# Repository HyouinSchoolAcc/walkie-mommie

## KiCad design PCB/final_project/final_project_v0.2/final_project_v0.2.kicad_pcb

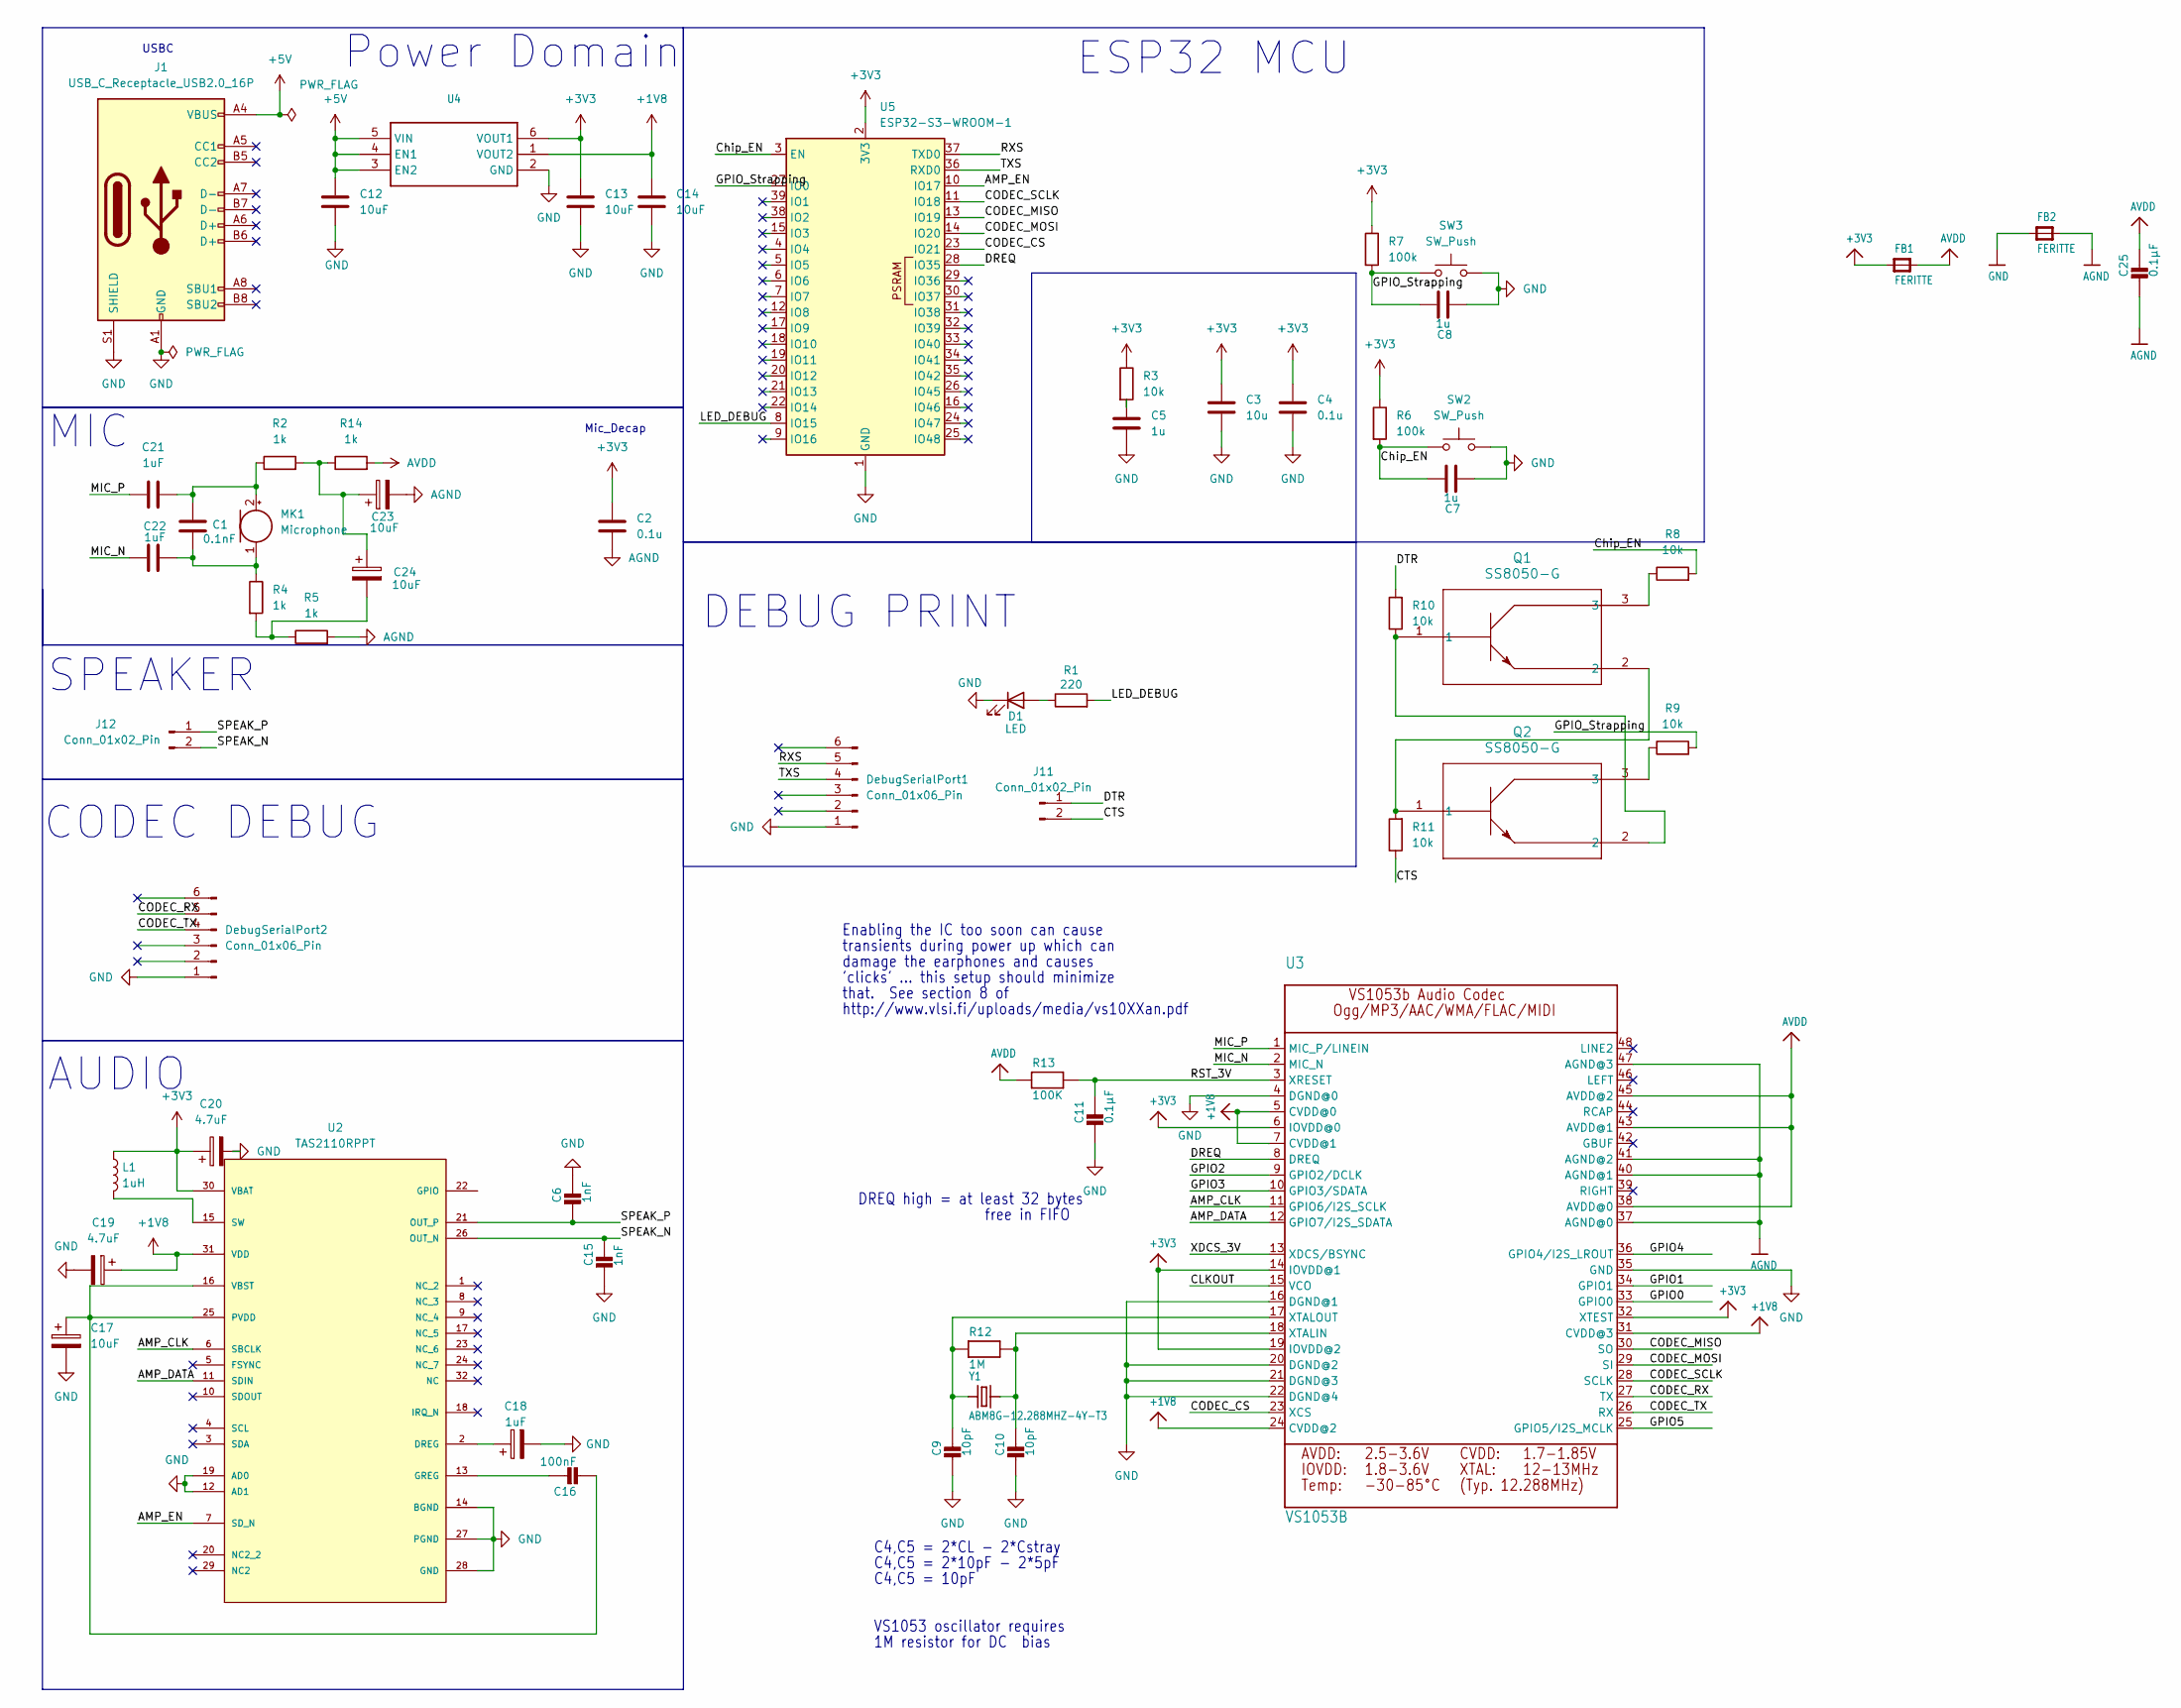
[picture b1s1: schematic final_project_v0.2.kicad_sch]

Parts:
C1: 0.1nF; C_0805_2012Metric_Pad1.18x1.45mm_HandSolder
C2, C4: 0.1u; C_0805_2012Metric_Pad1.18x1.45mm_HandSolder
C3: 10u; C_0805_2012Metric_Pad1.18x1.45mm_HandSolder
C5, C7, C8: 1u; C_0805_2012Metric_Pad1.18x1.45mm_HandSolder
C6, C15: 1nF; C_0805_2012Metric_Pad1.18x1.45mm_HandSolder
C9, C10: 10pF; C_0805_2012Metric_Pad1.18x1.45mm_HandSolder
C11, C25: 0.1µF; C_0805_2012Metric_Pad1.18x1.45mm_HandSolder
C12, C13, C14: 10uF; C_0805_2012Metric_Pad1.18x1.45mm_HandSolder
C16: 100nF; C_0805_2012Metric_Pad1.18x1.45mm_HandSolder
C17, C23, C24: 10uF; CP_Elec_6.3x5.4
C18: 1uF; CP_Elec_4x5.4
C19, C20: 4.7uF; CP_Elec_5x5.4
C21, C22: 1uF; C_0805_2012Metric_Pad1.18x1.45mm_HandSolder
D1: LED; LED_0805_2012Metric_Pad1.15x1.40mm_HandSolder
DebugSerialPort1, DebugSerialPort2: Conn_01x06_Pin; PinHeader_1x06_P2.54mm_Vertical
FB1, FB2: FERITTE; L_Walsin_WLFM201209x
J1: USB_C_Receptacle_USB2.0_16P; USB_C_Receptacle_GCT_USB4085
J11: Conn_01x02_Pin; PinHeader_1x02_P2.54mm_Vertical
J12: Conn_01x02_Pin; PinHeader_1x02_P1.00mm_Vertical_SMD_Pin1Left
L1: 1uH; L_1210_3225Metric
MK1: Microphone; MIC_CMA-4544PF-W
Q1, Q2: SS8050-G; TRAN_SS8050-G_CIP
R1: 220; R_0805_2012Metric_Pad1.20x1.40mm_HandSolder
R2, R4, R5, R14: 1k; C_0805_2012Metric_Pad1.18x1.45mm_HandSolder
R3, R8, R9, R10, R11: 10k; R_0805_2012Metric_Pad1.20x1.40mm_HandSolder
R6, R7: 100k; R_0805_2012Metric_Pad1.20x1.40mm_HandSolder
R12: 1M; R_0805_2012Metric_Pad1.20x1.40mm_HandSolder
R13: 100K; R_0805_2012Metric_Pad1.20x1.40mm_HandSolder
SW2, SW3: SW_Push; SW_PUSH_6mm_H4.3mm
U2: TAS2110RPPT; RPP0032A; PARTNUMBER TAS2110RPP
U3: VS1053B; LQFP48-0.5-7X7MM
U4: TSOT-23-6_D6_MCH
U5: ESP32-S3-WROOM-1
Y1: ABM8G-12.288MHZ-4Y-T3; Crystal_SMD_SeikoEpson_FA238-4Pin_3.2x2.5mm_HandSoldering

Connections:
+3V3: C2.1, C3.1, C4.1, C13.1, C20.1, FB1.1, L1.1, R3.1, R6.1, R7.1, U2.30 (VBAT), U3.6 (IOVDD@0), U3.14 (IOVDD@1), U3.19 (IOVDD@2), U3.32 (XTEST), U4.6 (VOUT1), U5.2 (3V3)
+5V: C12.1, J1.A4 (VBUS), J1.A9 (VBUS), J1.B4 (VBUS), J1.B9 (VBUS), U4.3 (EN2), U4.4 (EN1), U4.5 (VIN)
/AMP_CLK: U2.6 (SBCLK), U3.11 (GPIO6/I2S_SCLK)
/AMP_DATA: U2.11 (SDIN), U3.12 (GPIO7/I2S_SDATA)
/AMP_EN: U2.7 (SD_N), U5.10 (IO17)
/CLKOUT: U3.15 (VCO)
/CODEC_CS: U3.23 (XCS), U5.23 (IO21)
/CODEC_MISO: U3.30 (SO), U5.13 (IO19)
/CODEC_MOSI: U3.29 (SI), U5.14 (IO20)
/CODEC_RX: DebugSerialPort2.5, U3.27 (TX)
/CODEC_SCLK: U3.28 (SCLK), U5.11 (IO18)
/CODEC_TX: DebugSerialPort2.4, U3.26 (RX)
/CTS: J11.2, R11.1
/Chip_EN: C7.1, R6.2, R8.2, SW2.1, U5.3 (EN)
/DREQ: U3.8 (DREQ), U5.28 (IO35)
/DTR: J11.1, R10.2
/GPIO0: U3.33 (GPIO0)
/GPIO1: U3.34 (GPIO1)
/GPIO2: U3.9 (GPIO2/DCLK)
/GPIO3: U3.10 (GPIO3/SDATA)
/GPIO4: U3.36 (GPIO4/I2S_LROUT)
/GPIO5: U3.25 (GPIO5/I2S_MCLK)
/GPIO_Strapping: C8.1, R7.2, R9.2, SW3.1, U5.27 (IO0)
/LED_DEBUG: R1.2, U5.8 (IO15)
/MIC_N: C22.1, U3.2 (MIC_N)
/MIC_P: C21.1, U3.1 (MIC_P/LINEIN)
/RST_3V: C11.1, R13.2, U3.3 (XRESET)
/RXS: DebugSerialPort1.5, U5.37 (TXD0)
/SPEAK_N: C15.1, J12.2, U2.26 (OUT_N)
/SPEAK_P: C6.2, J12.1, U2.21 (OUT_P)
/TXS: DebugSerialPort1.4, U5.36 (RXD0)
/XDCS_3V: U3.13 (XDCS/BSYNC)
AGND: C2.2, C23.2, C25.2, FB2.2, R5.2, U3.37 (AGND@0), U3.40 (AGND@1), U3.41 (AGND@2), U3.47 (AGND@3)
AVDD: C25.1, FB1.2, R13.1, R14.2, U3.38 (AVDD@0), U3.43 (AVDD@1), U3.45 (AVDD@2)
GND: C3.2, C4.2, C5.2, C6.1, C7.2, C8.2, C9.2, C10.2, C11.2, C12.2, C13.2, C14.2, C15.2, C17.2, C18.2, C19.2, C20.2, D1.1 (K), DebugSerialPort1.1, DebugSerialPort2.1, FB2.1, J1.A1 (GND), J1.A12 (GND), J1.B1 (GND), J1.B12 (GND), J1.S1 (SHIELD), SW2.2, SW3.2, U2.12 (AD1), U2.14 (BGND), U2.19 (AD0), U2.27 (PGND), U2.28 (GND), U3.4 (DGND@0), U3.16 (DGND@1), U3.20 (DGND@2), U3.21 (DGND@3), U3.22 (DGND@4), U3.35 (GND), U4.2 (GND), U5.1 (GND), U5.40 (GND), U5.41 (GND)
unnamed: C5.1, R3.2
unnamed: C23.1, C24.1, R2.2, R14.1
unnamed: C24.2, R4.2, R5.1
unnamed: D1.2 (A), R1.1
unnamed: C1.1, C21.2, MK1.2 (+), R2.1
unnamed: C1.2, C22.2, MK1.1 (-), R4.1
unnamed: Q1.1, Q2.2, R10.1
unnamed: Q1.2, Q2.1, R11.2
unnamed: Q1.3, R8.1
unnamed: Q2.3, R9.1
unnamed: C18.1, U2.2 (DREG)
unnamed: C16.1, U2.13 (GREG)
unnamed: C16.2, C17.1, U2.16 (VBST), U2.25 (PVDD)
unnamed: L1.2, U2.15 (SW)
unnamed: C10.1, R12.2, U3.18 (XTALIN), Y1.2
unnamed: C9.1, R12.1, U3.17 (XTALOUT), Y1.1

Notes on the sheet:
VS1053 oscillator requires
SPEAKER
AUDIO
Mic_Decap
Power Domain
transients during power up which can
DREQ high = at least 32 bytes
C4,C5 = 2*CL - 2*Cstray
Enabling the IC too soon can cause
CODEC DEBUG
USBC
ESP32 MCU
MIC
1M resistor for DC bias
C4,C5 = 2*10pF - 2*5pF
C4,C5 = 10pF
'clicks' ... this setup should minimize
free in FIFO
DEBUG PRINT
http://www.vlsi.fi/uploads/media/vs10XXan.pdf
that. See section 8 of
damage the earphones and causes

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
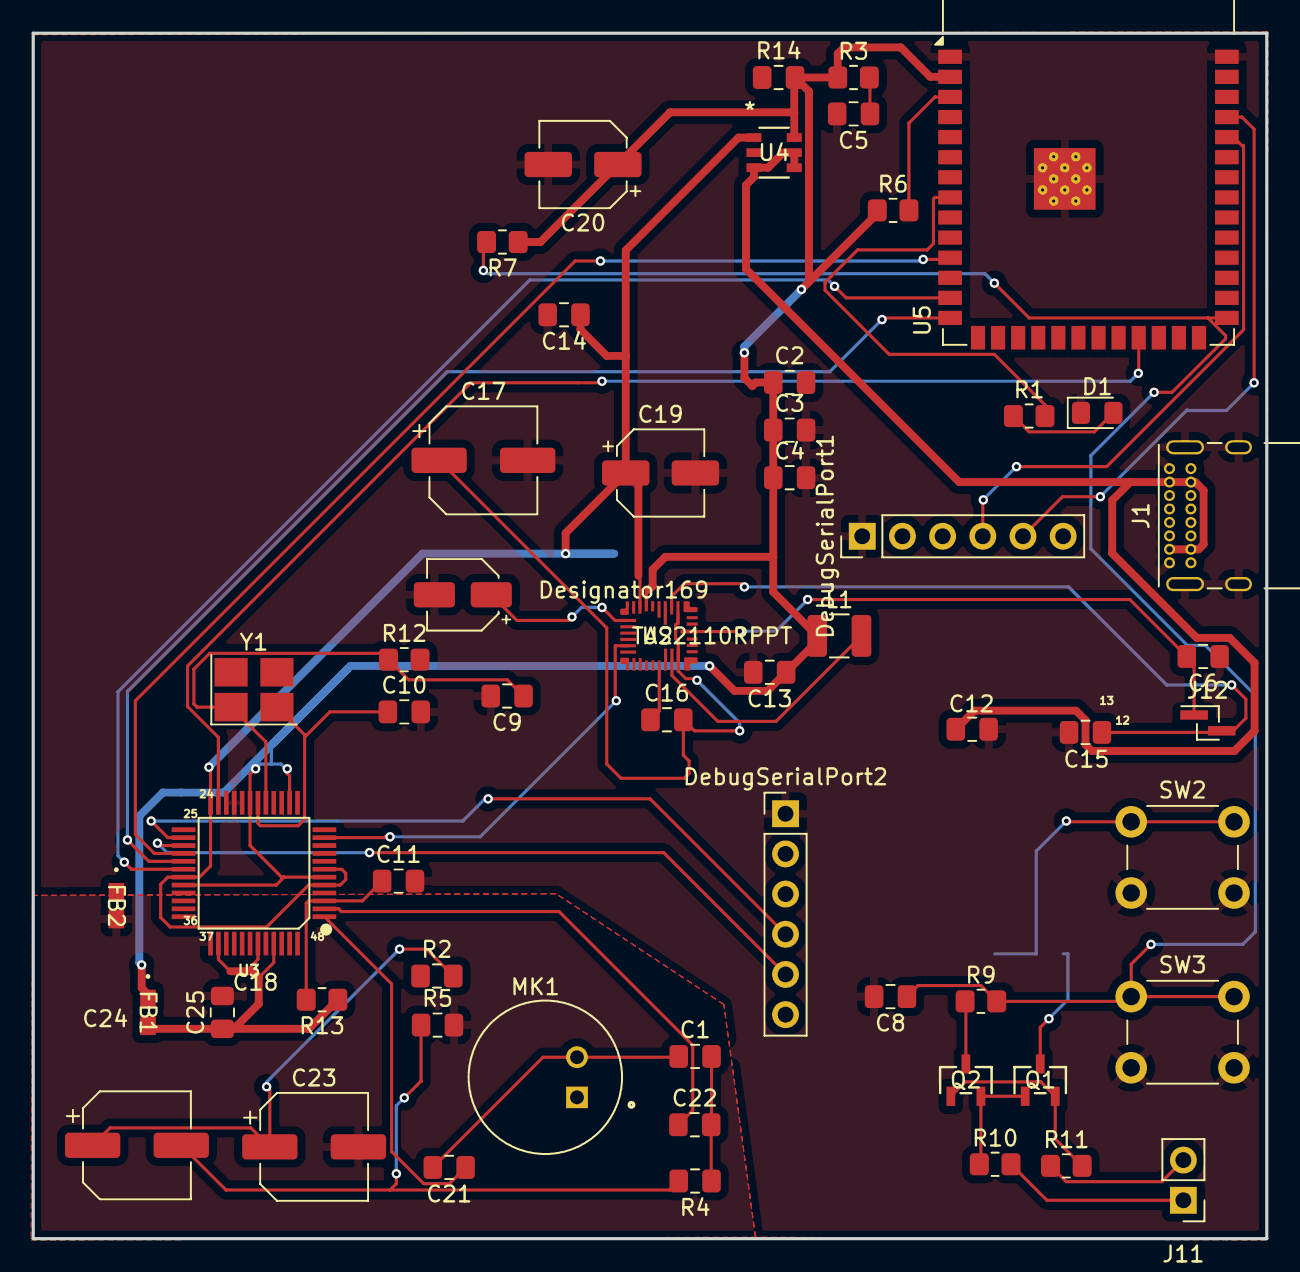
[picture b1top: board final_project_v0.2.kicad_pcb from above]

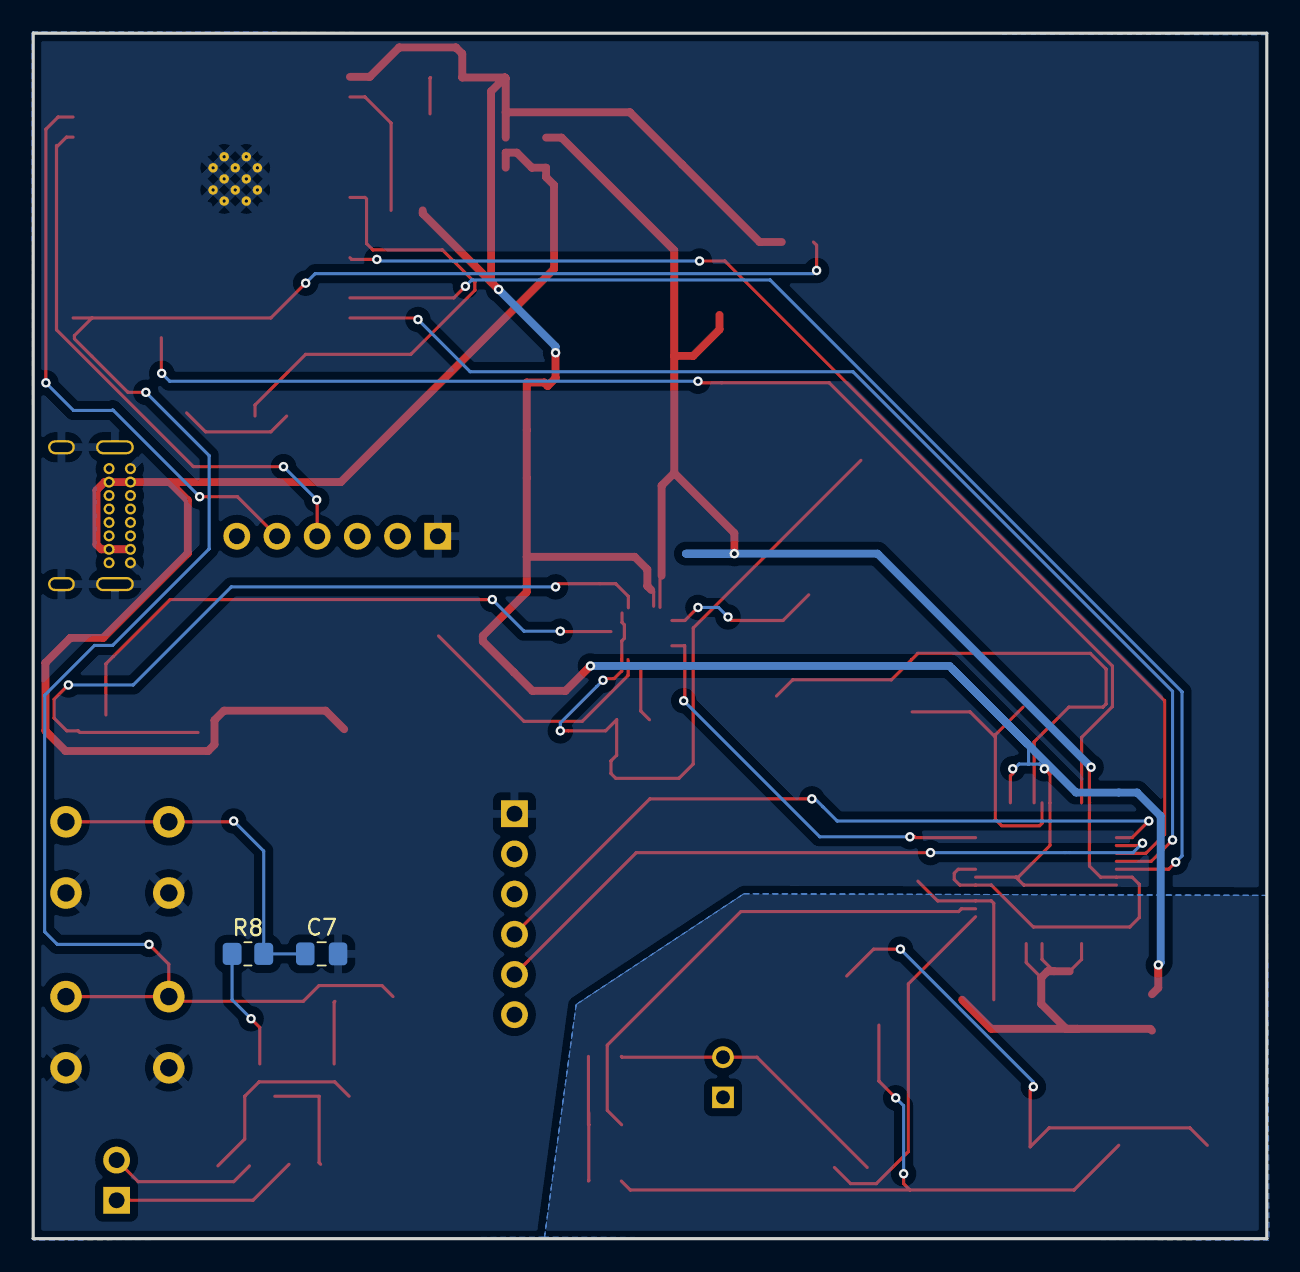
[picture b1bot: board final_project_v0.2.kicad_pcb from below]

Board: 2 copper layers, 78.0 x 76.2 mm, 58 parts (2 on the bottom side), 45 nets.

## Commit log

2024-12-29 added original cad files in
2025-01-06 added libs
2025-01-06 more lib stuff
2025-01-22 pushing new schem
2025-01-24 Add files via upload
    Upload initial VS1053b schematic
2025-01-31 finished! yippee!
